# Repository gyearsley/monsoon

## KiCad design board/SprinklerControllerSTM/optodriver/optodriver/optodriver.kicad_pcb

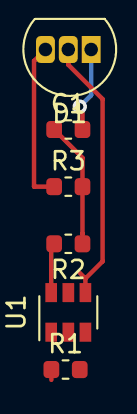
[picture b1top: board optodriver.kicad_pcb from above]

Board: 2 copper layers, 6 parts (0 on the bottom side), 6 nets.

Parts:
C1: 0.1uf; C_0603_1608Metric
D1: Q_TRIAC_A1GA2; TO-92L_Inline
R1: 500; R_0603_1608Metric
R2: 180; R_0603_1608Metric
R3: 2.4K; R_0603_1608Metric
U1: MOC3010M; SOT-23-6

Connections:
/AC0: D1.3, R3.1
/AC1: C1.2, D1.1
unnamed: C1.1, R2.1, R3.2
unnamed: D1.2, U1.4
unnamed: R1.1, U1.1
unnamed: R2.2, U1.6

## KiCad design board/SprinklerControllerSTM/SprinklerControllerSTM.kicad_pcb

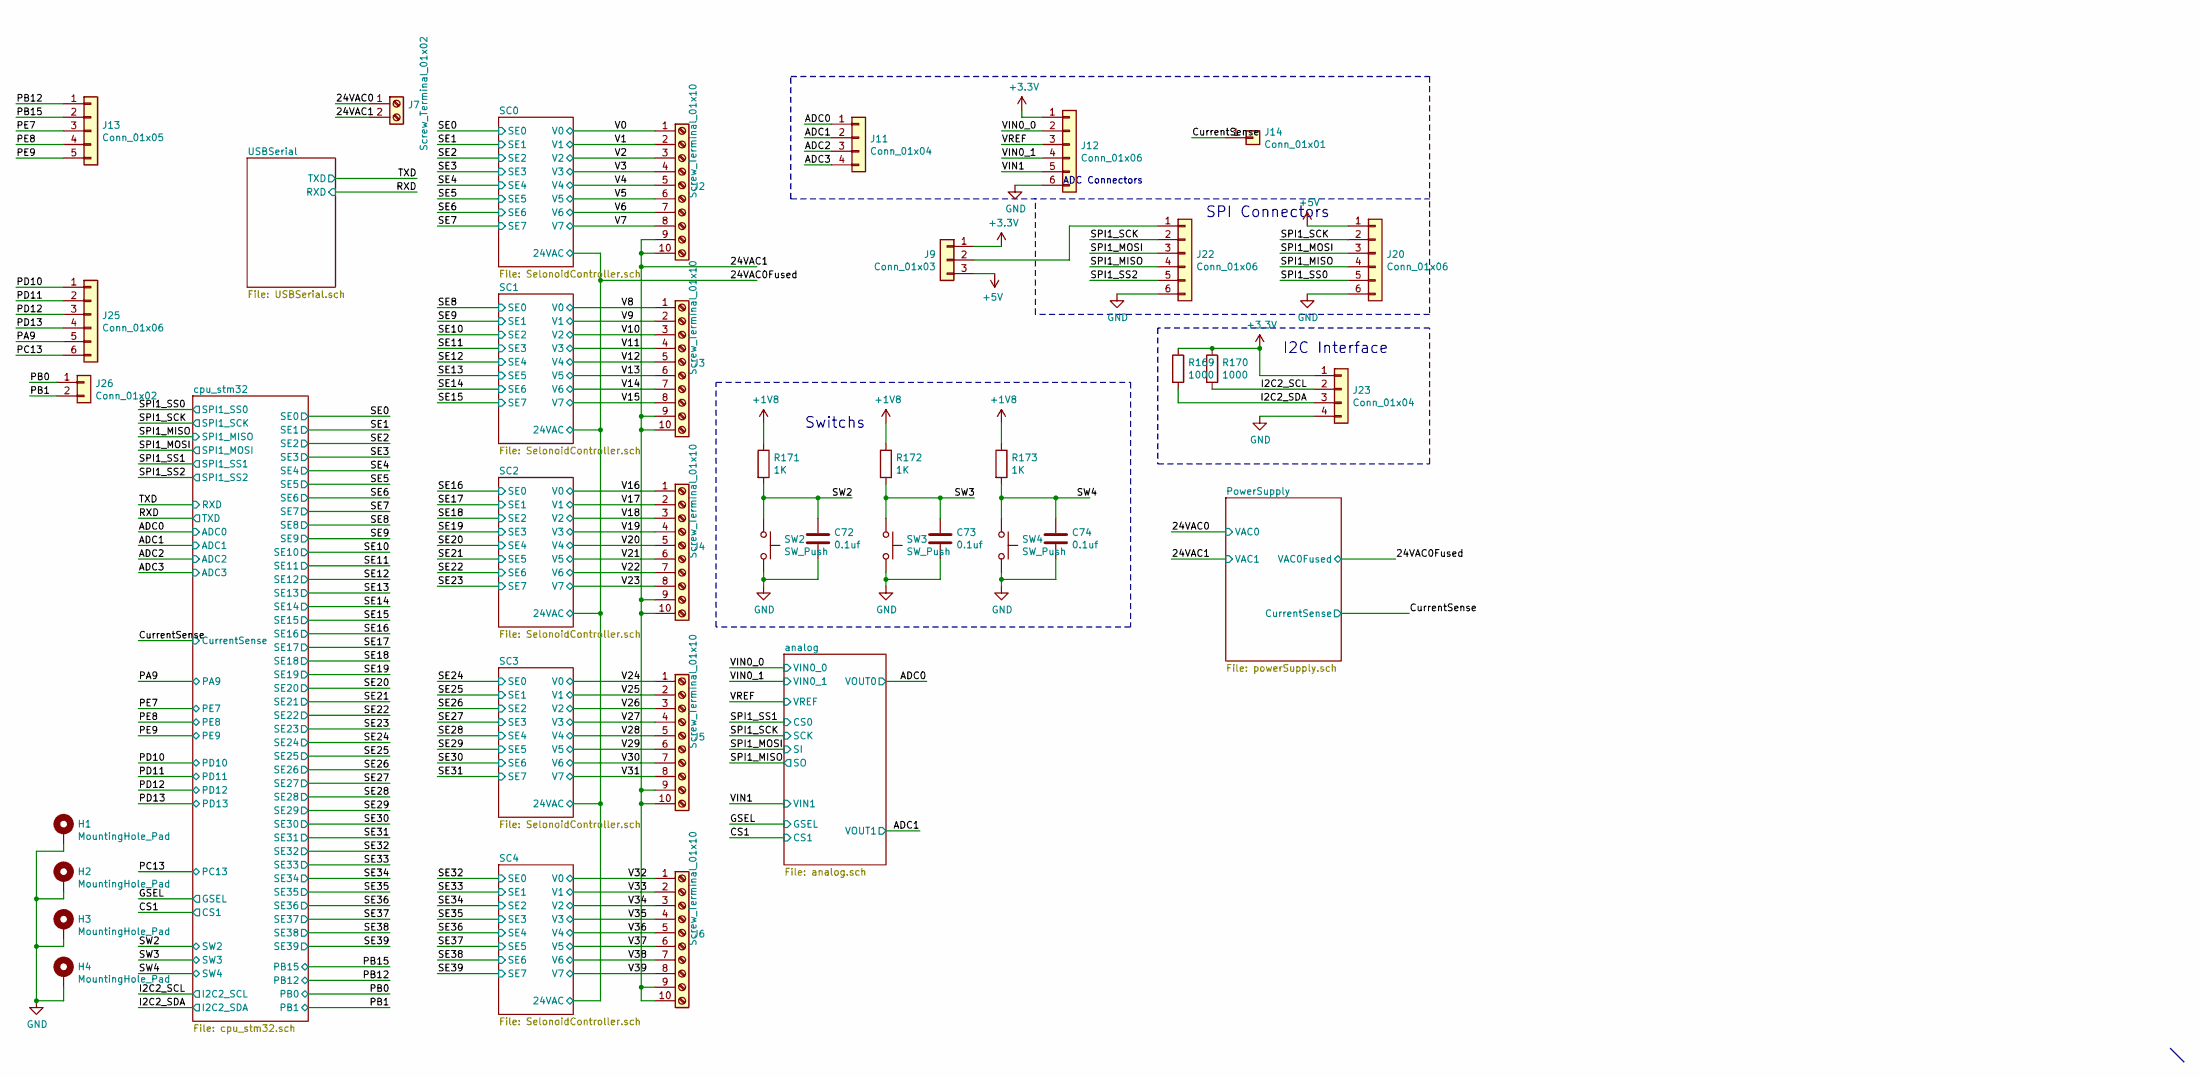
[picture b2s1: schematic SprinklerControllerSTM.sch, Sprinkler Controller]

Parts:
C72, C73, C74: 0.1uf; C_0603_1608Metric
H1, H2, H3, H4: MountingHole_Pad; MountingHole_2.7mm_M2.5_ISO7380_Pad
J2, J3, J4, J5, J6: Screw_Terminal_01x10; PinHeader_1x10_P2.54mm_Horizontal
J7: Screw_Terminal_01x02; PinHeader_1x02_P2.54mm_Vertical
J9: Conn_01x03; PinHeader_1x03_P2.54mm_Vertical
J11, J23: Conn_01x04; PinHeader_1x04_P2.54mm_Vertical
J12, J20, J22, J25: Conn_01x06; PinHeader_1x06_P2.54mm_Vertical
J13: Conn_01x05; PinHeader_1x05_P2.54mm_Vertical
J14: Conn_01x01; PinHeader_1x01_P2.54mm_Vertical
J26: Conn_01x02; PinHeader_1x02_P2.54mm_Vertical
R169, R170: 1000; R_0603_1608Metric
R171, R172, R173: 1K; R_0603_1608Metric
SW2, SW3, SW4: SW_Push; series_95C_switch_spst_pb_smd

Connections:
+1V8: R171.1, R172.1, R173.1; also elsewhere on the board
+3V3: J9.1, J12.1, J23.1, R169.1, R170.1; also elsewhere on the board
+5V: J9.3, J20.1; also elsewhere on the board
/24VAC0: J7.1; also elsewhere on the board
/24VAC1: J2.9, J2.10, J3.9, J3.10, J4.9, J4.10, J5.9, J5.10, J6.9, J6.10, J7.2; also elsewhere on the board
/ADC0: J11.1; also elsewhere on the board
/ADC1: J11.2; also elsewhere on the board
/ADC2: J11.3; also elsewhere on the board
/ADC3: J11.4; also elsewhere on the board
/CurrentSense: J14.1; also elsewhere on the board
/I2C2_SCL: J23.2, R170.2; also elsewhere on the board
/I2C2_SDA: J23.3, R169.2; also elsewhere on the board
/PA9: J25.5; also elsewhere on the board
/PB0: J26.1; also elsewhere on the board
/PB1: J26.2; also elsewhere on the board
/PB12: J13.1; also elsewhere on the board
/PB15: J13.2; also elsewhere on the board
/PC13: J25.6; also elsewhere on the board
/PD10: J25.1; also elsewhere on the board
/PD11: J25.2; also elsewhere on the board
/PD12: J25.3; also elsewhere on the board
/PD13: J25.4; also elsewhere on the board
/PE7: J13.3; also elsewhere on the board
/PE8: J13.4; also elsewhere on the board
/PE9: J13.5; also elsewhere on the board
/SPI1_MISO: J20.4, J22.4; also elsewhere on the board
/SPI1_MOSI: J20.3, J22.3; also elsewhere on the board
/SPI1_SCK: J20.2, J22.2; also elsewhere on the board
/SPI1_SS0: J20.5; also elsewhere on the board
/SPI1_SS2: J22.5; also elsewhere on the board
/SW2: C72.1, R171.2, SW2.1; also elsewhere on the board
/SW3: C73.1, R172.2, SW3.1; also elsewhere on the board
/SW4: C74.1, R173.2, SW4.1; also elsewhere on the board
/V0: J2.1; also elsewhere on the board
/V1: J2.2; also elsewhere on the board
/V2: J2.3; also elsewhere on the board
/V3: J2.4; also elsewhere on the board
/V4: J2.5; also elsewhere on the board
/V5: J2.6; also elsewhere on the board
/V6: J2.7; also elsewhere on the board
/V7: J2.8; also elsewhere on the board
/V8: J3.1; also elsewhere on the board
/V9: J3.2; also elsewhere on the board
/V10: J3.3; also elsewhere on the board
/V11: J3.4; also elsewhere on the board
/V12: J3.5; also elsewhere on the board
/V13: J3.6; also elsewhere on the board
/V14: J3.7; also elsewhere on the board
/V15: J3.8; also elsewhere on the board
/V16: J4.1; also elsewhere on the board
/V17: J4.2; also elsewhere on the board
/V18: J4.3; also elsewhere on the board
/V19: J4.4; also elsewhere on the board
/V20: J4.5; also elsewhere on the board
/V21: J4.6; also elsewhere on the board
/V22: J4.7; also elsewhere on the board
/V23: J4.8; also elsewhere on the board
/V24: J5.1; also elsewhere on the board
/V25: J5.2; also elsewhere on the board
/V26: J5.3; also elsewhere on the board
/V27: J5.4; also elsewhere on the board
/V28: J5.5; also elsewhere on the board
/V29: J5.6; also elsewhere on the board
/V30: J5.7; also elsewhere on the board
/V31: J5.8; also elsewhere on the board
/V32: J6.1; also elsewhere on the board
/V33: J6.2; also elsewhere on the board
/V34: J6.3; also elsewhere on the board
/V35: J6.4; also elsewhere on the board
/V36: J6.5; also elsewhere on the board
/V37: J6.6; also elsewhere on the board
/V38: J6.7; also elsewhere on the board
/V39: J6.8; also elsewhere on the board
/VIN0_0: J12.2; also elsewhere on the board
/VIN0_1: J12.4; also elsewhere on the board
/VIN1: J12.5; also elsewhere on the board
/VREF: J12.3; also elsewhere on the board
GND: C72.2, C73.2, C74.2, H1.1, H2.1, H3.1, H4.1, J12.6, J20.6, J22.6, J23.4, SW2.2, SW3.2, SW4.2; also elsewhere on the board
unnamed: J9.2, J22.1

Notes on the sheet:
SPI Connectors
ADC Connectors
I2C Interface
Switchs

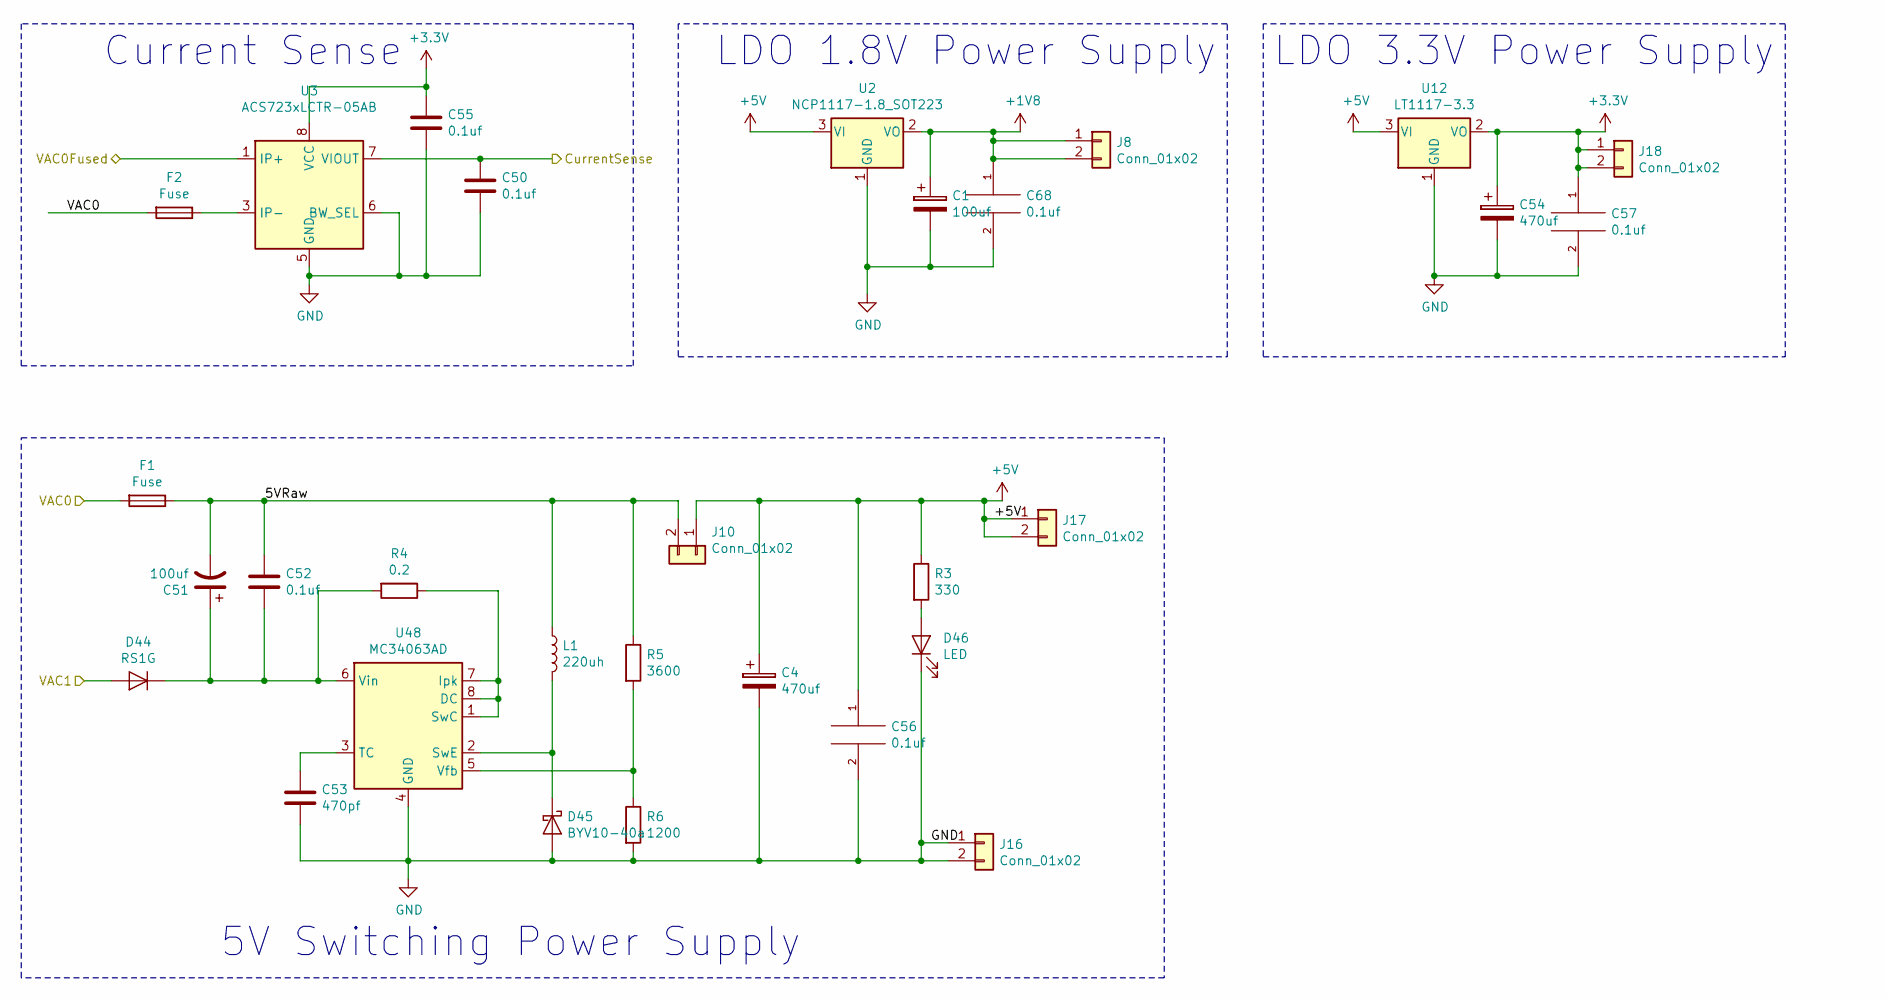
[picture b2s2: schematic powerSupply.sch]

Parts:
C1, C51: 100uf; CP_Radial_D6.3mm_P2.50mm
C4, C54: 470uf; CP_Radial_D6.3mm_P2.50mm
C50, C52, C55, C56, C57, C68: 0.1uf; C_0603_1608Metric
C53: 470pf; C_0603_1608Metric
D44: RS1G; DO-214AC
D45: BYV10-40a; Schottky_diode_TMBYV_10_40
D46: LED; led_lxt0805gw_tr
F1: Fuse; Bourns_resettable_fuse
F2: Fuse; OG_Clip_5x20
J8, J10, J16, J17, J18: Conn_01x02; PinHeader_1x02_P2.54mm_Vertical
L1: 220uh; Taiyo_inductor_10050
R3: 330; R_0603_1608Metric
R4: 0.2; R_0603_1608Metric
R5: 3600; R_0603_1608Metric
R6: 1200; R_0603_1608Metric
U2: NCP1117-1.8_SOT223; SOT-223-3_TabPin2
U3: ACS723xLCTR-05AB; SOIC-8_3.9x4.9mm_P1.27mm
U12: LT1117-3.3; SOT-223-3_TabPin2
U48: MC34063AD; SOIC-8_3.9x4.9mm_P1.27mm

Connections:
+1V8: C1.1, C68.1, J8.1, J8.2, U2.2 (VO); also elsewhere on the board
+3V3: C54.1, C55.1, C57.1, J18.1, J18.2, U3.8 (VCC), U12.2 (VO); also elsewhere on the board
+5V: C4.1, C56.1, J10.1, J17.1, J17.2, R3.1, U2.3 (VI), U12.3 (VI); also elsewhere on the board
/24VAC0: F1.2, F2.2; also elsewhere on the board
/24VAC0Fused: U3.1 (IP+), U3.2 (IP+); also elsewhere on the board
/24VAC1: D44.2 (A); also elsewhere on the board
/CurrentSense: C50.1, U3.7 (VIOUT); also elsewhere on the board
/PowerSupply/5VRaw: C51.2, C52.1, F1.1, J10.2, L1.1, R5.1
GND: C1.2, C4.2, C50.2, C53.2, C54.2, C55.2, C56.2, C57.2, C68.2, D45.2 (A), D46.1 (K), J16.1, J16.2, R6.2, U2.1 (GND), U3.5 (GND), U3.6 (BW_SEL), U12.1 (GND), U48.4 (GND); also elsewhere on the board
unnamed: C51.1, C52.2, D44.1 (K), R4.2, U48.6 (Vin)
unnamed: C53.1, U48.3 (TC)
unnamed: D45.1 (K), L1.2, U48.2 (SwE)
unnamed: D46.2 (A), R3.2
unnamed: F2.1, U3.3 (IP-), U3.4 (IP-)
unnamed: R4.1, U48.1 (SwC), U48.7 (Ipk), U48.8 (DC)
unnamed: R5.2, R6.1, U48.5 (Vfb)

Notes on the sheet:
Current Sense
LDO 1.8V Power Supply
LDO 3.3V Power Supply
5V Switching Power Supply

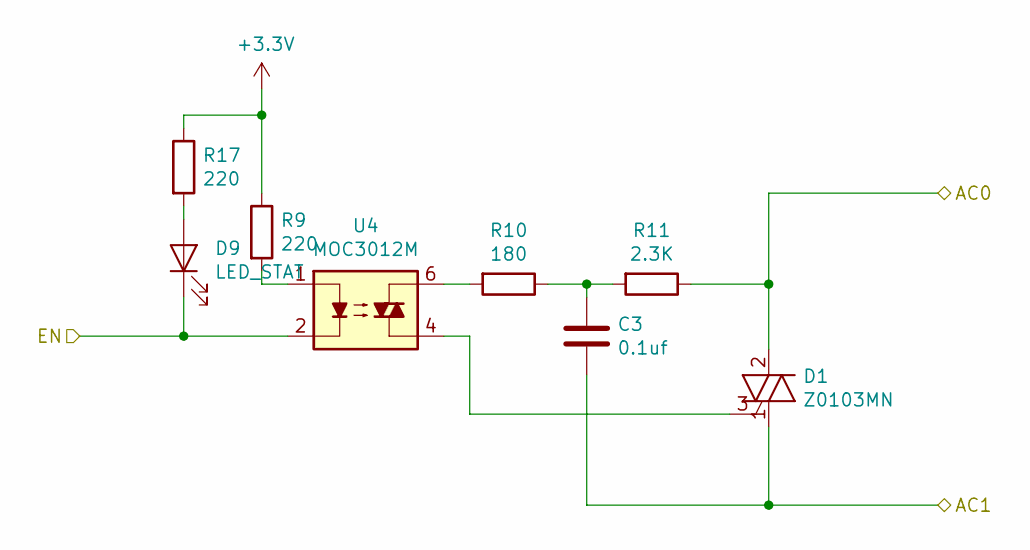
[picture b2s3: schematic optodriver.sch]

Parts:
C3: 0.1uf; C_0603_1608Metric
D1: Z0103MN; SOT-223
D9: LED_STAT; LED_0603_1608Metric
R9, R17: 220; R_0603_1608Metric
R10: 180; R_0603_1608Metric
R11: 2.3K; R_0603_1608Metric
U4: MOC3012M; SMDIP-6_W9.53mm

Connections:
+3V3: R9.1, R17.1; also elsewhere on the board
/24VAC0Fused: D1.2 (A2), D1.4 (A4), R11.1; also elsewhere on the board
/SE0: D9.1 (K), U4.2; also elsewhere on the board
/V0: C3.2, D1.1 (A1); also elsewhere on the board
unnamed: C3.1, R10.1, R11.2
unnamed: D1.3 (G), U4.4
unnamed: D9.2 (A), R17.2
unnamed: R9.2, U4.1
unnamed: R10.2, U4.6

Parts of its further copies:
C9, C10, C11, C12, C13, C14, C15, C16, C17, C18, C19, C20, C21, C22, C23, C24, C25, C26, C27, C28, C29, C30, C31, C32, C33, C34, C35, C36, C37, C38, C39, C40, C41, C42, C43, C44, C45, C46, C47: 0.1uf; C_0603_1608Metric
D2, D3, D4, D5, D6, D7, D8, D11, D12, D13, D14, D15, D16, D17, D18, D19, D20, D21, D22, D23, D24, D25, D26, D27, D28, D29, D30, D31, D32, D33, D34, D35, D36, D37, D38, D39, D40, D41, D42: Z0103MN; SOT-223
D10, D48, D49, D50, D51, D52, D53, D54, D55, D56, D57, D58, D59, D60, D61, D62, D63, D64, D65, D66, D67, D68, D69, D70, D71, D72, D73, D74, D75, D76, D77, D78, D79, D80, D81, D82, D83, D84, D85: LED_STAT; LED_0603_1608Metric
R12, R15, R18, R19, R20, R21, R22, R23, R24, R25, R26, R28, R31, R34, R35, R36, R37, R38, R39, R40, R41, R42, R45, R48, R51, R52, R53, R54, R55, R56, R57, R58, R59, R62, R65, R67, R68, R69, R70, R71, R72, R73, R74, R76, R79, R82, R85, R88, R91, R94, R97, R100, R103, R106, R109, R112, R115, R118, R121, R124, R127, R130, R133, R136, R139, R142, R145, R148, R151, R154, R157, R160, R163, R164, R165, R166, R167, R168: 220; R_0603_1608Metric
R13, R16, R29, R32, R43, R46, R49, R60, R63, R66, R77, R80, R83, R86, R89, R92, R95, R98, R101, R104, R107, R110, R113, R116, R119, R122, R125, R128, R131, R134, R137, R140, R143, R146, R149, R152, R155, R158, R161: 180; R_0603_1608Metric
R14, R27, R30, R33, R44, R47, R50, R61, R64, R75, R78, R81, R84, R87, R90, R93, R96, R99, R102, R105, R108, R111, R114, R117, R120, R123, R126, R129, R132, R135, R138, R141, R144, R147, R150, R153, R156, R159, R162: 2.3K; R_0603_1608Metric
U5, U6, U7, U8, U9, U10, U11, U13, U14, U15, U16, U17, U18, U19, U20, U22, U23, U24, U25, U26, U27, U28, U29, U31, U32, U33, U34, U35, U36, U37, U38, U40, U41, U42, U43, U44, U45, U46, U47: MOC3012M; SMDIP-6_W9.53mm

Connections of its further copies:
+3V3: R12.1, R15.1, R18.1, R19.1, R20.1, R21.1, R22.1, R23.1, R24.1, R25.1, R26.1, R28.1, R31.1, R34.1, R35.1, R36.1, R37.1, R38.1, R39.1, R40.1, R41.1, R42.1, R45.1, R48.1, R51.1, R52.1, R53.1, R54.1, R55.1, R56.1, R57.1, R58.1, R59.1, R62.1, R65.1, R67.1, R68.1, R69.1, R70.1, R71.1, R72.1, R73.1, R74.1, R76.1, R79.1, R82.1, R85.1, R88.1, R91.1, R94.1, R97.1, R100.1, R103.1, R106.1, R109.1, R112.1, R115.1, R118.1, R121.1, R124.1, R127.1, R130.1, R133.1, R136.1, R139.1, R142.1, R145.1, R148.1, R151.1, R154.1, R157.1, R160.1, R163.1, R164.1, R165.1, R166.1, R167.1, R168.1; also elsewhere on the board
/24VAC0Fused: D2.2 (A2), D2.4 (A4), D3.2 (A2), D3.4 (A4), D4.2 (A2), D4.4 (A4), D5.2 (A2), D5.4 (A4), D6.2 (A2), D6.4 (A4), D7.2 (A2), D7.4 (A4), D8.2 (A2), D8.4 (A4), D11.2 (A2), D11.4 (A4), D12.2 (A2), D12.4 (A4), D13.2 (A2), D13.4 (A4), D14.2 (A2), D14.4 (A4), D15.2 (A2), D15.4 (A4), D16.2 (A2), D16.4 (A4), D17.2 (A2), D17.4 (A4), D18.2 (A2), D18.4 (A4), D19.2 (A2), D19.4 (A4), D20.2 (A2), D20.4 (A4), D21.2 (A2), D21.4 (A4), D22.2 (A2), D22.4 (A4), D23.2 (A2), D23.4 (A4), D24.2 (A2), D24.4 (A4), D25.2 (A2), D25.4 (A4), D26.2 (A2), D26.4 (A4), D27.2 (A2), D27.4 (A4), D28.2 (A2), D28.4 (A4), D29.2 (A2), D29.4 (A4), D30.2 (A2), D30.4 (A4), D31.2 (A2), D31.4 (A4), D32.2 (A2), D32.4 (A4), D33.2 (A2), D33.4 (A4), D34.2 (A2), D34.4 (A4), D35.2 (A2), D35.4 (A4), D36.2 (A2), D36.4 (A4), D37.2 (A2), D37.4 (A4), D38.2 (A2), D38.4 (A4), D39.2 (A2), D39.4 (A4), D40.2 (A2), D40.4 (A4), D41.2 (A2), D41.4 (A4), D42.2 (A2), D42.4 (A4), R14.1, R27.1, R30.1, R33.1, R44.1, R47.1, R50.1, R61.1, R64.1, R75.1, R78.1, R81.1, R84.1, R87.1, R90.1, R93.1, R96.1, R99.1, R102.1, R105.1, R108.1, R111.1, R114.1, R117.1, R120.1, R123.1, R126.1, R129.1, R132.1, R135.1, R138.1, R141.1, R144.1, R147.1, R150.1, R153.1, R156.1, R159.1, R162.1; also elsewhere on the board
/SE1: D50.1 (K), U8.2; also elsewhere on the board
/SE2: D10.1 (K), U5.2; also elsewhere on the board
/SE3: D51.1 (K), U9.2; also elsewhere on the board
/SE4: D48.1 (K), U6.2; also elsewhere on the board
/SE5: D52.1 (K), U10.2; also elsewhere on the board
/SE6: D49.1 (K), U7.2; also elsewhere on the board
/SE7: D53.1 (K), U11.2; also elsewhere on the board
/SE8: D54.1 (K), U22.2; also elsewhere on the board
/SE9: D58.1 (K), U26.2; also elsewhere on the board
/SE10: D55.1 (K), U23.2; also elsewhere on the board
/SE11: D59.1 (K), U27.2; also elsewhere on the board
/SE12: D56.1 (K), U24.2; also elsewhere on the board
/SE13: D60.1 (K), U28.2; also elsewhere on the board
/SE14: D57.1 (K), U25.2; also elsewhere on the board
/SE15: D61.1 (K), U29.2; also elsewhere on the board
/SE16: D62.1 (K), U40.2; also elsewhere on the board
/SE17: D66.1 (K), U44.2; also elsewhere on the board
/SE18: D63.1 (K), U41.2; also elsewhere on the board
/SE19: D67.1 (K), U45.2; also elsewhere on the board
/SE20: D64.1 (K), U42.2; also elsewhere on the board
/SE21: D68.1 (K), U46.2; also elsewhere on the board
/SE22: D65.1 (K), U43.2; also elsewhere on the board
/SE23: D69.1 (K), U47.2; also elsewhere on the board
/SE24: D70.1 (K), U31.2; also elsewhere on the board
/SE25: D74.1 (K), U35.2; also elsewhere on the board
/SE26: D71.1 (K), U32.2; also elsewhere on the board
/SE27: D75.1 (K), U36.2; also elsewhere on the board
/SE28: D72.1 (K), U33.2; also elsewhere on the board
/SE29: D76.1 (K), U37.2; also elsewhere on the board
/SE30: D73.1 (K), U34.2; also elsewhere on the board
/SE31: D77.1 (K), U38.2; also elsewhere on the board
/SE32: D78.1 (K), U13.2; also elsewhere on the board
/SE33: D82.1 (K), U17.2; also elsewhere on the board
/SE34: D79.1 (K), U14.2; also elsewhere on the board
/SE35: D83.1 (K), U18.2; also elsewhere on the board
/SE36: D80.1 (K), U15.2; also elsewhere on the board
/SE37: D84.1 (K), U19.2; also elsewhere on the board
/SE38: D81.1 (K), U16.2; also elsewhere on the board
/SE39: D85.1 (K), U20.2; also elsewhere on the board
/V1: C12.2, D5.1 (A1); also elsewhere on the board
/V2: C9.2, D2.1 (A1); also elsewhere on the board
/V3: C13.2, D6.1 (A1); also elsewhere on the board
/V4: C10.2, D3.1 (A1); also elsewhere on the board
/V5: C14.2, D7.1 (A1); also elsewhere on the board
/V6: C11.2, D4.1 (A1); also elsewhere on the board
/V7: C15.2, D8.1 (A1); also elsewhere on the board
/V8: C24.2, D19.1 (A1); also elsewhere on the board
/V9: C28.2, D23.1 (A1); also elsewhere on the board
/V10: C25.2, D20.1 (A1); also elsewhere on the board
/V11: C29.2, D24.1 (A1); also elsewhere on the board
/V12: C26.2, D21.1 (A1); also elsewhere on the board
/V13: C30.2, D25.1 (A1); also elsewhere on the board
/V14: C27.2, D22.1 (A1); also elsewhere on the board
/V15: C31.2, D26.1 (A1); also elsewhere on the board
/V16: C40.2, D35.1 (A1); also elsewhere on the board
/V17: C44.2, D39.1 (A1); also elsewhere on the board
/V18: C41.2, D36.1 (A1); also elsewhere on the board
/V19: C45.2, D40.1 (A1); also elsewhere on the board
/V20: C42.2, D37.1 (A1); also elsewhere on the board
/V21: C46.2, D41.1 (A1); also elsewhere on the board
/V22: C43.2, D38.1 (A1); also elsewhere on the board
/V23: C47.2, D42.1 (A1); also elsewhere on the board
/V24: C32.2, D27.1 (A1); also elsewhere on the board
/V25: C36.2, D31.1 (A1); also elsewhere on the board
/V26: C33.2, D28.1 (A1); also elsewhere on the board
/V27: C37.2, D32.1 (A1); also elsewhere on the board
/V28: C34.2, D29.1 (A1); also elsewhere on the board
/V29: C38.2, D33.1 (A1); also elsewhere on the board
/V30: C35.2, D30.1 (A1); also elsewhere on the board
/V31: C39.2, D34.1 (A1); also elsewhere on the board
/V32: C16.2, D11.1 (A1); also elsewhere on the board
/V33: C20.2, D15.1 (A1); also elsewhere on the board
/V34: C17.2, D12.1 (A1); also elsewhere on the board
/V35: C21.2, D16.1 (A1); also elsewhere on the board
/V36: C18.2, D13.1 (A1); also elsewhere on the board
/V37: C22.2, D17.1 (A1); also elsewhere on the board
/V38: C19.2, D14.1 (A1); also elsewhere on the board
/V39: C23.2, D18.1 (A1); also elsewhere on the board
unnamed: C9.1, R13.1, R14.2
unnamed: C10.1, R16.1, R27.2
unnamed: C11.1, R29.1, R30.2
unnamed: C12.1, R32.1, R33.2
unnamed: C13.1, R43.1, R44.2
unnamed: C14.1, R46.1, R47.2
unnamed: C15.1, R49.1, R50.2
unnamed: C16.1, R60.1, R61.2
unnamed: C17.1, R63.1, R64.2
unnamed: C18.1, R66.1, R75.2
unnamed: C19.1, R77.1, R78.2
unnamed: C20.1, R80.1, R81.2
unnamed: C21.1, R83.1, R84.2
unnamed: C22.1, R86.1, R87.2
unnamed: C23.1, R89.1, R90.2
unnamed: C24.1, R92.1, R93.2
unnamed: C25.1, R95.1, R96.2
unnamed: C26.1, R98.1, R99.2
unnamed: C27.1, R101.1, R102.2
unnamed: C28.1, R104.1, R105.2
unnamed: C29.1, R107.1, R108.2
unnamed: C30.1, R110.1, R111.2
unnamed: C31.1, R113.1, R114.2
unnamed: C32.1, R116.1, R117.2
unnamed: C33.1, R119.1, R120.2
unnamed: C34.1, R122.1, R123.2
unnamed: C35.1, R125.1, R126.2
unnamed: C36.1, R128.1, R129.2
unnamed: C37.1, R131.1, R132.2
unnamed: C38.1, R134.1, R135.2
unnamed: C39.1, R137.1, R138.2
unnamed: C40.1, R140.1, R141.2
unnamed: C41.1, R143.1, R144.2
unnamed: C42.1, R146.1, R147.2
unnamed: C43.1, R149.1, R150.2
unnamed: C44.1, R152.1, R153.2
unnamed: C45.1, R155.1, R156.2
unnamed: C46.1, R158.1, R159.2
unnamed: C47.1, R161.1, R162.2
unnamed: D2.3 (G), U5.4
unnamed: D3.3 (G), U6.4
unnamed: D4.3 (G), U7.4
unnamed: D5.3 (G), U8.4
unnamed: D6.3 (G), U9.4
unnamed: D7.3 (G), U10.4
unnamed: D8.3 (G), U11.4
unnamed: D10.2 (A), R18.2
unnamed: D11.3 (G), U13.4
unnamed: D12.3 (G), U14.4
unnamed: D13.3 (G), U15.4
unnamed: D14.3 (G), U16.4
unnamed: D15.3 (G), U17.4
unnamed: D16.3 (G), U18.4
unnamed: D17.3 (G), U19.4
unnamed: D18.3 (G), U20.4
unnamed: D19.3 (G), U22.4
unnamed: D20.3 (G), U23.4
unnamed: D21.3 (G), U24.4
unnamed: D22.3 (G), U25.4
unnamed: D23.3 (G), U26.4
unnamed: D24.3 (G), U27.4
unnamed: D25.3 (G), U28.4
unnamed: D26.3 (G), U29.4
unnamed: D27.3 (G), U31.4
unnamed: D28.3 (G), U32.4
unnamed: D29.3 (G), U33.4
unnamed: D30.3 (G), U34.4
unnamed: D31.3 (G), U35.4
unnamed: D32.3 (G), U36.4
unnamed: D33.3 (G), U37.4
unnamed: D34.3 (G), U38.4
unnamed: D35.3 (G), U40.4
unnamed: D36.3 (G), U41.4
unnamed: D37.3 (G), U42.4
unnamed: D38.3 (G), U43.4
unnamed: D39.3 (G), U44.4
unnamed: D40.3 (G), U45.4
unnamed: D41.3 (G), U46.4
unnamed: D42.3 (G), U47.4
unnamed: D48.2 (A), R19.2
unnamed: D49.2 (A), R20.2
unnamed: D50.2 (A), R21.2
unnamed: D51.2 (A), R22.2
unnamed: D52.2 (A), R23.2
unnamed: D53.2 (A), R24.2
unnamed: D54.2 (A), R25.2
unnamed: D55.2 (A), R26.2
unnamed: D56.2 (A), R35.2
unnamed: D57.2 (A), R36.2
unnamed: D58.2 (A), R37.2
unnamed: D59.2 (A), R38.2
unnamed: D60.2 (A), R39.2
unnamed: D61.2 (A), R40.2
unnamed: D62.2 (A), R41.2
unnamed: D63.2 (A), R42.2
unnamed: D64.2 (A), R51.2
unnamed: D65.2 (A), R52.2
unnamed: D66.2 (A), R53.2
unnamed: D67.2 (A), R54.2
unnamed: D68.2 (A), R55.2
unnamed: D69.2 (A), R56.2
unnamed: D70.2 (A), R57.2
unnamed: D71.2 (A), R58.2
unnamed: D72.2 (A), R67.2
unnamed: D73.2 (A), R68.2
unnamed: D74.2 (A), R69.2
unnamed: D75.2 (A), R70.2
unnamed: D76.2 (A), R71.2
unnamed: D77.2 (A), R72.2
unnamed: D78.2 (A), R73.2
unnamed: D79.2 (A), R74.2
unnamed: D80.2 (A), R163.2
unnamed: D81.2 (A), R164.2
unnamed: D82.2 (A), R165.2
unnamed: D83.2 (A), R166.2
unnamed: D84.2 (A), R167.2
unnamed: D85.2 (A), R168.2
unnamed: R12.2, U5.1
unnamed: R13.2, U5.6
unnamed: R15.2, U6.1
unnamed: R16.2, U6.6
unnamed: R28.2, U7.1
unnamed: R29.2, U7.6
unnamed: R31.2, U8.1
unnamed: R32.2, U8.6
unnamed: R34.2, U9.1
unnamed: R43.2, U9.6
unnamed: R45.2, U10.1
unnamed: R46.2, U10.6
unnamed: R48.2, U11.1
unnamed: R49.2, U11.6
unnamed: R59.2, U13.1
unnamed: R60.2, U13.6
unnamed: R62.2, U14.1
unnamed: R63.2, U14.6
unnamed: R65.2, U15.1
unnamed: R66.2, U15.6
unnamed: R76.2, U16.1
unnamed: R77.2, U16.6
unnamed: R79.2, U17.1
unnamed: R80.2, U17.6
unnamed: R82.2, U18.1
unnamed: R83.2, U18.6
unnamed: R85.2, U19.1
unnamed: R86.2, U19.6
unnamed: R88.2, U20.1
unnamed: R89.2, U20.6
unnamed: R91.2, U22.1
unnamed: R92.2, U22.6
unnamed: R94.2, U23.1
unnamed: R95.2, U23.6
unnamed: R97.2, U24.1
unnamed: R98.2, U24.6
unnamed: R100.2, U25.1
unnamed: R101.2, U25.6
unnamed: R103.2, U26.1
unnamed: R104.2, U26.6
unnamed: R106.2, U27.1
unnamed: R107.2, U27.6
unnamed: R109.2, U28.1
unnamed: R110.2, U28.6
unnamed: R112.2, U29.1
unnamed: R113.2, U29.6
unnamed: R115.2, U31.1
unnamed: R116.2, U31.6
unnamed: R118.2, U32.1
unnamed: R119.2, U32.6
unnamed: R121.2, U33.1
unnamed: R122.2, U33.6
unnamed: R124.2, U34.1
unnamed: R125.2, U34.6
unnamed: R127.2, U35.1
unnamed: R128.2, U35.6
unnamed: R130.2, U36.1
unnamed: R131.2, U36.6
unnamed: R133.2, U37.1
unnamed: R134.2, U37.6
unnamed: R136.2, U38.1
unnamed: R137.2, U38.6
unnamed: R139.2, U40.1
unnamed: R140.2, U40.6
unnamed: R142.2, U41.1
unnamed: R143.2, U41.6
unnamed: R145.2, U42.1
unnamed: R146.2, U42.6
unnamed: R148.2, U43.1
unnamed: R149.2, U43.6
unnamed: R151.2, U44.1
unnamed: R152.2, U44.6
unnamed: R154.2, U45.1
unnamed: R155.2, U45.6
unnamed: R157.2, U46.1
unnamed: R158.2, U46.6
unnamed: R160.2, U47.1
unnamed: R161.2, U47.6
